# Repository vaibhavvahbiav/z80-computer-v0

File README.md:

Z80 8-bit computer design (For educational purposes only).

The main motive for making this computer design was pure intrigue in retro computers, working of computers and overall interest in computational electronics.

I chose Z80 specifically, because it is one of the greatest 8 bit CPUs / microprocessors ever made. It can be compared to the great 6502.

Z80 is also an easier to understand microprocessor and is easily available across the world at affordable prices.
This Design is a student project, for the students. This design was the first iteration of the design I am trying to achieve. It is completely messy.
But i will be constantly try to make this is a better piece of hardware.
This project has many problems and scopes of improvements which are highlighted in the mistakes and scopes of improvement file.

When I started working on this project, I started learning about the various delays, clock signals, control signals and how does z80 computes, stores and outputs.
This helped me learn about how computers work in a broader sense, as it created a basic idea about it.

The Zilog Z80 is a 8 bit microprocessor which can operate from 4MHz to 20MHz (Much higher in newer versions).
It is slow enough to make students understand the working, while fast enough to be considered a Consumer computer.

The build here uses 8Kb of ROM, 8Kb of RAM, a PPI (Parallel Peripheral Interface) with 3 ports for external I/O devices like keyboards and a latch to display a output in LEDs(didnt want to use Display as it increased complexities).

The PCB was the first attempt at doing work at Computational electronics stuff, as it shows that nothing is structured and everything is just like cooper noodles on a plate.

This publication is an attempt to get feedback from everyone regarding improvements, and changes that are required to make the build better so that i can create a much better piece of hardware.

Designed by - Vaibhav A.

GitHub - https://github.com/vaibhavvahbiav

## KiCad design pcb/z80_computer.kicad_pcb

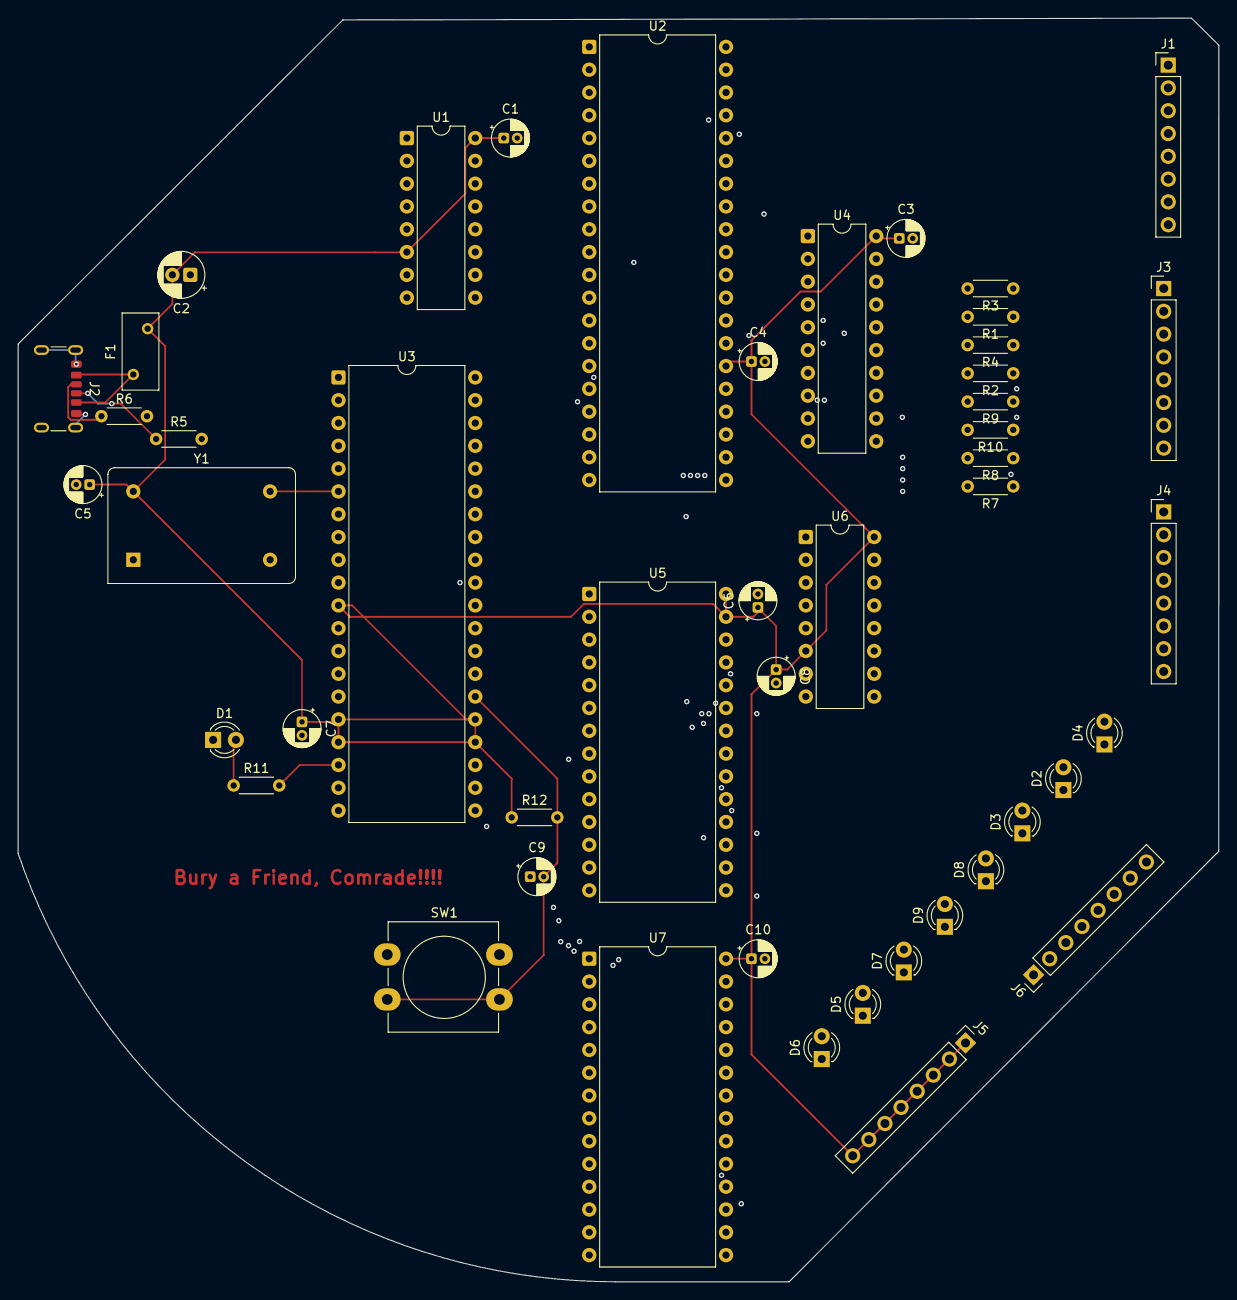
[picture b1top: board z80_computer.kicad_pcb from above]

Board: 10 copper layers, 133.8 x 140.8 mm, 47 parts (0 on the bottom side), 81 nets.

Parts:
C1, C3, C4, C5, C6, C7, C8, C10: 0.1u; CP_Radial_D4.0mm_P1.50mm
C2: 10u; CP_Radial_D5.0mm_P2.00mm
C9: 100nF; CP_Radial_D4.0mm_P1.50mm
D1, D2, D3, D4, D5, D6, D7, D8, D9: LED; LED_D3.0mm
F1: Polyfuse_Small; Fuse_BelFuse_0ZRE0005FF_L8.3mm_W3.8mm
J1, J3, J4, J5, J6: Conn_01x08_Pin; PinHeader_1x08_P2.54mm_Vertical
J2: USB_C_Receptacle_PowerOnly_6P; USB_C_Receptacle_GCT_USB4125-xx-x-0190_6P_TopMnt_Horizontal
R1, R2, R3, R4, R7, R8, R9, R10, R11: 220; R_Axial_DIN0204_L3.6mm_D1.6mm_P5.08mm_Horizontal
R5, R6: 5.1k; R_Axial_DIN0204_L3.6mm_D1.6mm_P5.08mm_Horizontal
R12: 5k; R_Axial_DIN0204_L3.6mm_D1.6mm_P5.08mm_Horizontal
SW1: SW_Push; SW_PUSH-12mm_Wuerth-430476085716
U1, U6: 74HC138; CERDIP-16_W7.62mm_SideBrazed
U2: 8255; DIP-40_W15.24mm
U3: Z84C00xxP; DIP-40_W15.24mm
U4: 74LS373; CERDIP-20_W7.62mm_SideBrazed
U5: KM28C64A; DIP-28_W15.24mm
U7: HM62256BLP; DIP-28_W15.24mm
Y1: ACO-xxxMHz; Oscillator_DIP-14

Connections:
+5V: C1.1, C2.2, C3.1, C4.1, C5.1, C6.1, C7.1, C8.1, C10.1, F1.2, J5.1, J5.2, J5.3, J5.4, J5.5, J5.6, J5.7, J5.8, R12.1, U1.6 (E2), U1.16 (VCC), U2.26 (VCC), U3.11 (V_{CC}), U3.16 (~INT), U3.17 (~NMI), U3.24 (~WAIT), U3.25 (~BUSREQ), U4.20 (VCC), U5.27 (~WE), U5.28 (VCC), U6.6 (E2), U6.16 (VCC), U7.28 (VCC), Y1.14 (Vcc)
/A2: U1.3 (A2), U3.32 (A_{2}), U5.8 (A2), U7.8 (A2)
/A3: U3.33 (A_{3}), U5.7 (A3), U7.7 (A3)
/A4: U3.34 (A_{4}), U5.6 (A4), U7.6 (A4)
/A5: U3.35 (A_{5}), U5.5 (A5), U7.5 (A5)
/A6: U3.36 (A_{6}), U5.4 (A6), U7.4 (A6)
/A7: U3.37 (A_{7}), U5.3 (A7), U7.3 (A7)
/A8: U3.38 (A_{8}), U5.25 (A8), U7.25 (A8)
/A9: U3.39 (A_{9}), U5.24 (A9), U7.24 (A9)
/A10: U3.40 (A_{10}), U5.21 (A10), U7.21 (A10)
/A11: U3.1 (A_{11}), U5.23 (A11), U7.23 (A11)
/A12: U3.2 (A_{12}), U5.2 (A12), U7.2 (A12)
/A13: U3.3 (A_{13}), U6.1 (A0), U7.26 (A13)
/A14: U3.4 (A_{14}), U6.2 (A1), U7.1 (A14)
/A15: U3.5 (A_{15}), U6.3 (A2)
/D0: U2.34 (D0), U3.14 (D_{0}), U4.3 (D0), U5.11 (I/O0), U7.11 (Q0)
/D1: U2.33 (D1), U3.15 (D_{1}), U4.4 (D1), U5.12 (I/O1), U7.12 (Q1)
/D2: U2.32 (D2), U3.12 (D_{2}), U4.7 (D2), U5.13 (I/O2), U7.13 (Q2)
/D3: U2.31 (D3), U3.8 (D_{3}), U4.8 (D3), U5.15 (I/O3), U7.15 (Q3)
/D4: U2.30 (D4), U3.7 (D_{4}), U4.13 (D4), U5.16 (I/O4), U7.16 (Q4)
/D5: U2.29 (D5), U3.9 (D_{5}), U4.14 (D5), U5.17 (I/O5), U7.17 (Q5)
/D6: U2.28 (D6), U3.10 (D_{6}), U4.17 (D6), U5.18 (I/O6), U7.18 (Q6)
/D7: U2.27 (D7), U3.13 (D_{7}), U4.18 (D7), U5.19 (I/O7), U7.19 (Q7)
A0: U1.1 (A0), U2.9 (A0), U3.30 (A_{0}), U5.10 (A0), U7.10 (A0)
A1: U1.2 (A1), U2.8 (A1), U3.31 (A_{1}), U5.9 (A1), U7.9 (A1)
GND: C1.2, C2.1, C3.2, C4.2, C5.2, C6.2, C7.2, C8.2, C9.1, C10.2, D1.1 (K), D2.1 (K), D3.1 (K), D4.1 (K), D5.1 (K), D6.1 (K), D7.1 (K), D8.1 (K), D9.1 (K), J2.A12 (GND), J2.B12 (GND), J2.S1 (SHIELD), J6.1, J6.2, J6.3, J6.4, J6.5, J6.6, J6.7, J6.8, R5.2, R6.2, SW1.1, U1.4 (~E0), U1.8 (GND), U2.7 (GND), U3.29 (GND), U4.1 (OE), U4.10 (GND), U5.14 (GND), U6.4 (~E0), U6.8 (GND), U7.14 (GND), Y1.7 (GND)
unnamed: D1.2 (A), R11.1
unnamed: D6.2 (A), R7.1
unnamed: D5.2 (A), R8.1
unnamed: D7.2 (A), R10.1
unnamed: D9.2 (A), R9.1
unnamed: D8.2 (A), R2.1
unnamed: D3.2 (A), R4.1
unnamed: D2.2 (A), R1.1
unnamed: D4.2 (A), R3.1
unnamed: F1.1, J2.A9 (VBUS), J2.B9 (VBUS)
unnamed: J4.1, U2.4 (PA0)
unnamed: J4.2, U2.3 (PA1)
unnamed: J4.3, U2.2 (PA2)
unnamed: J4.4, U2.1 (PA3)
unnamed: J4.5, U2.40 (PA4)
unnamed: J4.6, U2.39 (PA5)
unnamed: J4.7, U2.38 (PA6)
unnamed: J4.8, U2.37 (PA7)
unnamed: J3.1, U2.18 (PB0)
unnamed: J3.2, U2.19 (PB1)
unnamed: J3.3, U2.20 (PB2)
unnamed: J3.4, U2.21 (PB3)
unnamed: J3.5, U2.22 (PB4)
unnamed: J3.6, U2.23 (PB5)
unnamed: J3.7, U2.24 (PB6)
unnamed: J3.8, U2.25 (PB7)
unnamed: J1.1, U2.14 (PC0)
unnamed: J1.2, U2.15 (PC1)
unnamed: J1.3, U2.16 (PC2)
unnamed: J1.4, U2.17 (PC3)
unnamed: J1.5, U2.13 (PC4)
unnamed: J1.6, U2.12 (PC5)
unnamed: J1.7, U2.11 (PC6)
unnamed: J1.8, U2.10 (PC7)
unnamed: J2.A5 (CC1), R6.1
unnamed: J2.B5 (CC2), R5.1
unnamed: U3.6 (CLK), Y1.8 (OUT)
unnamed: R11.2, U3.18 (~HALT)
unnamed: R7.2, U4.2 (O0)
unnamed: R8.2, U4.5 (O1)
unnamed: R10.2, U4.6 (O2)
unnamed: R9.2, U4.9 (O3)
unnamed: R2.2, U4.12 (O4)
unnamed: R4.2, U4.15 (O5)
unnamed: R1.2, U4.16 (O6)
unnamed: R3.2, U4.19 (O7)
/CE RAM: U6.14 (~Y1), U7.20 (~CS)
/CE ROM: U5.20 (~CE), U6.15 (~Y0)
/CS: U1.13 (~Y2), U2.6 (~CS)
/IORQ: U1.5 (~E1), U3.20 (~IORQ)
/LE: U1.15 (~Y0), U4.11 (LE)
/MREQ: U3.19 (~MREQ), U6.5 (~E1)
/RD: U2.5 (~RD), U3.21 (~RD), U5.22 (~OE), U7.22 (~OE)
/RESET: C9.2, R12.2, SW1.2, U2.35 (RESET), U3.26 (~RESET)
/WR: U2.36 (~WR), U3.22 (~WR), U7.27 (~WE)

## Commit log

2026-01-01 pcb x-ray view
2026-01-01 Block diagram for the computer
2026-01-01 mistakes-and-scope-of-improvement.md
2026-01-02 README.md
2026-01-02 Z80 computer schematics
2026-01-02 Schematic Files
2026-01-02 PCB file for the Z80 computer
2026-01-02 Schematics for Z80 computer
2026-01-02 Documents related to the Z80 Computer
2026-01-02 3D view for Z80 Computer
2026-01-02 bomv
2026-01-02 Bill of Materials for the Z80 Computer
